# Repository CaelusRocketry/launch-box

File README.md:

View this project on [CADLAB.io](https://cadlab.io/project/25442). 

# Launch Box
Source code for our rocket's launch box.

# Pre-refactor
https://github.com/ProjectCaelus/launch-box/tree/2eb651392b1af030fa2c863ca12c2973148bd2ff

# Making Changes
Post-production version of PCBs: those currently in use are in launch-box\_stable folders. You shouldn't be editing these files, only copying them or using them as reference
Libraries now stores all our libraries
2 schematic libraries: CaelusPCB.lib and Launchbox.lib
1 Footprint library: Launchbox.pretty
If you intend to make a change to a PCB, copy the most recent version's project directory, in this case it should be those in _stable, rename, and move it to launch-box\PCBs\{corresponding folder}
Follow the naming conventions: Date + Time + Name
First off, it's important that you know what files you should and should not edit.
There are 3 kinds of libraries:

1.) -.lib: Looks like CaelusPCB.lib or Launchbox.lib
These are our stable global project libraries, meaning that they are like the framework for all components in all projects

2.) -cache.lib
When you copy a project directory, its -cache.lib file is copied with it. If you make changes to the schematic, for example adding a new component, the local -cache.lib file will update. The -cache.lib of the copied project remains the same, and this is how we do version control.
You don't need to really know how this process works or why its important. You just need to know that you add components to -.lib directories. YOU DON'T TOUCH -cache.lib or -rescue.lib.

3.) -rescue.lib
Not important until you're ready to publish/push your changes.
Whenever you copy a new project, or pull from github, YOU NEED TO CHECK YOUR LIBRARIES
Make sure that you have CaelusPCB.lib or Launchbox.lib (depending on what project you're working on, pointing to launch-box\Libraries\CaelusPCB.lib or Launchbox.lib
Make sure in Manage Footprints libraries, you have launch-box\Libaries\launchbox.pretty
Make sure the -cache and -rescue files are in the correct project directory: not from the copied one or something random
When you're finished on a project, you need to do the following:

1.) Make sure everything is saved, close and reopen KiCad

2.) Delete, not uncheck, Delete Launchbox.lib and/or CaelusPCB.lib from your library preferences and reopen the schematic.

3.) You should be prompted to rescue your -cached files. Say ok to all.

  This updates your -rescue.lib and sets all your schematic components to read from -rescue.lib instead of CaelusPCB.lib or Launchbox.lib
  This means this project is now isolated: a change in the global project libraries won't change your project

4.) Message avionics lead to verify and git push.

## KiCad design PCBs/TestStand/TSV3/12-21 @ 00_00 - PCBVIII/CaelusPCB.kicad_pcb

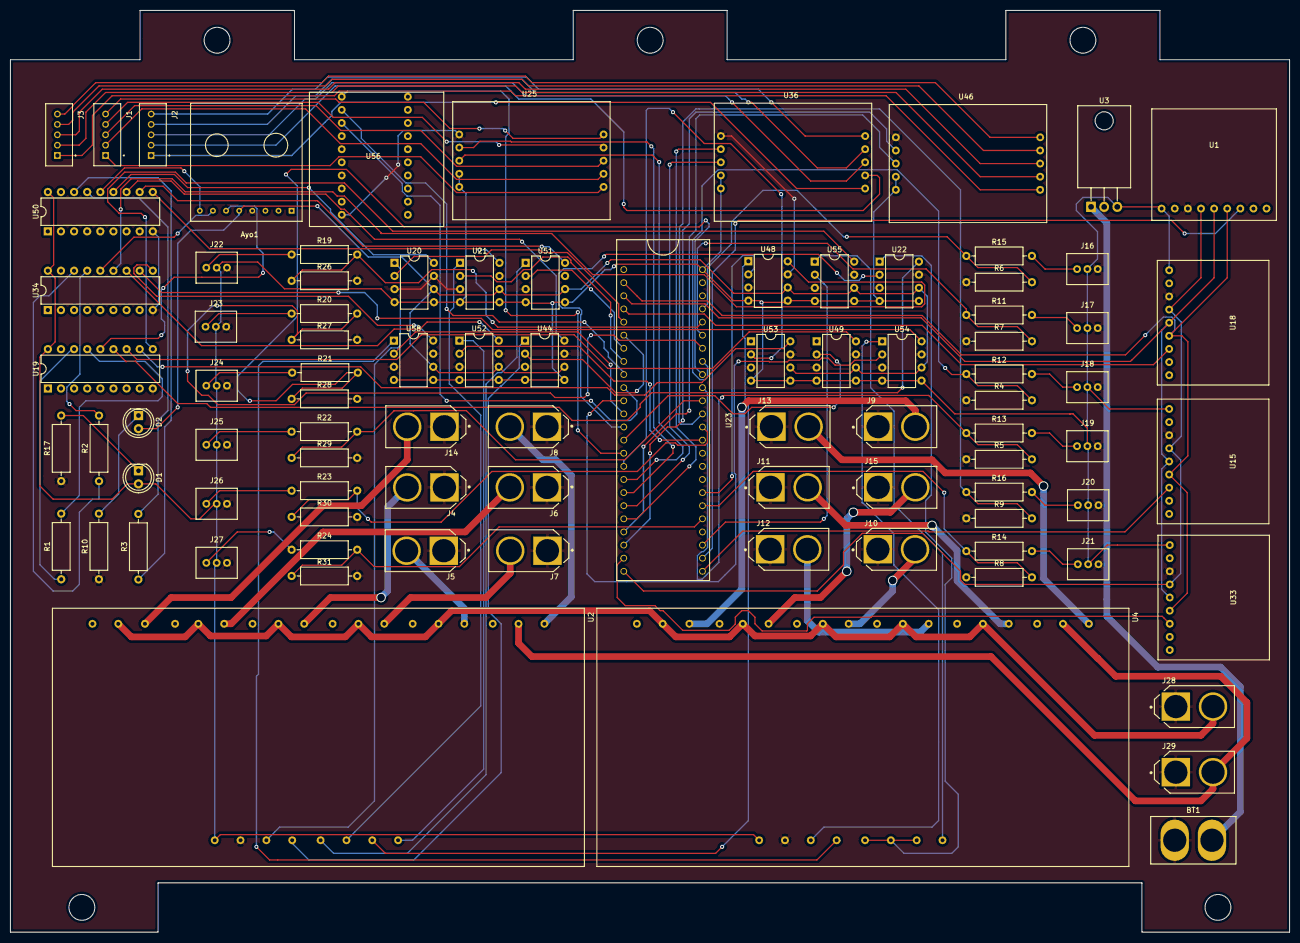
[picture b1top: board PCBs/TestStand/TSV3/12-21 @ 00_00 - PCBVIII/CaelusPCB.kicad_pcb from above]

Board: 2 copper layers, 247.7 x 178.4 mm, 89 parts (0 on the bottom side), 118 nets.

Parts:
Ayo1: RJ45EthernetBreakout
BT1: Battery_Cell; XT60H-M12
D1, D2: LED; LED_D5.0mm
J1, J2, J3: 440055-5; TE_1735446-5
J4, J5, J6, J7, J8, J9, J10, J11, J12, J13, J14, J15: XT60-M; AMASS_XT60-M
J16, J17, J18, J19, J20, J21, J22, J23, J24, J25, J26, J27: 440055-3; Crimp_Header
J28, J29: CaelusPCB-rescue_XT60-M-CaelusPCB; AMASS_XT60-M
R1, R2, R3, R4, R5, R6, R7, R8, R9, R11, R12, R13, R14, R15, R16, R19, R20, R21, R22, R23, R24, R26, R27, R28, R29, R30, R31: R_US; R_Axial_DIN0309_L9.0mm_D3.2mm_P12.70mm_Horizontal
R10, R17: R; R_Axial_DIN0309_L9.0mm_D3.2mm_P12.70mm_Horizontal
U1, U15, U18, U33: MAX31856
U2, U4: 6-Channel-5V-Relays; 6x_relay_module
U3: L7805; TO-220-3_Horizontal_TabDown
U19, U34, U50: Launchbox_HT12D; DIP-18_W7.62mm
U20, U21, U22, U44, U48, U49, U51, U52, U53, U54, U55, U58: SPDT_IC; DIP-8_W7.62mm
U23: Teensy3.6; Teensy 3.6
U25, U36, U46: LoadCellAmp
U56: XBee_Breakout; Xbee_Breakout

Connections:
1: U1.4, U15.4, U18.4, U23.32, U33.4
2: U23.31, U33.7
3: U20.2, U23.3
3.3: U23.47, U56.1
4: U23.4, U44.2
5: U23.5, U51.2
6: U21.2, U23.6
7: U23.39, U48.2
8: U23.13, U52.2
9: U23.9, U54.2
10: U23.10, U58.2
11: U22.2, U23.11
12: U23.12, U49.2
13: U1.6, U15.6, U18.6, U23.0, U33.6
14: U1.5, U15.5, U18.5, U23.1, U33.5
15: U18.7, U23.2
16: U23.25, U25.8
17: U23.26, U25.7
18: U23.27, U36.8
19: U23.28, U36.7
20: U23.29, U46.8
21: U23.30, U46.7
25: Ayo1.8, U50.14
26: Ayo1.7, U34.14
27: Ayo1.6, U19.14
28: U20.8, U50.13
29: U44.8, U50.12
30: U50.11, U51.8
31: U21.8, U50.10
32: U34.13, U48.8
33: U34.12, U52.8
34: U34.11, U54.8
35: U34.10, U58.8
36: U19.13, U22.8
37: U19.12, U49.8
38: U19.11, U53.8
39: U19.10, U55.8
40: U2.3, U20.1
41: U2.4, U44.1
42: U2.5, U51.1
43: U2.6, U21.1
44: U2.7, U48.1
45: U2.8, U52.1
46: U4.3, U54.1
47: U4.4, U58.1
48: U4.5, U4.6, U4.7, U22.1
50: U15.7, U23.33
51: U1.7, U23.34
52: Ayo1.5, D2.2, U20.6, U21.6, U22.6, U44.6, U48.6, U49.6, U51.6, U52.6, U53.6, U54.6, U55.6, U58.6
54: U4.8, U55.1
57: U23.24, U53.2
58: U23.35, U55.2
60: U23.8, U56.3
61: U23.7, U56.2
62: J4.2, U2.17
63: J7.2, U2.20
64: J5.2, U2.23
65: J8.2, U2.26
66: J9.2, U4.11
67: J15.2, U4.14
68: J10.2, U4.17
69: J12.2, U4.20
70: J11.2, U4.23
71: J13.2, U4.26
80: J14.2, U2.11
81: J6.2, U2.14
+5V: D1.2, J16.2, J17.2, J18.2, J19.2, J20.2, J21.2, J22.2, J23.2, J24.2, J25.2, J26.2, J27.2, U1.1, U2.1, U3.3, U4.1, U15.1, U18.1, U19.18, U20.4, U20.5, U21.4, U21.5, U22.4, U22.5, U23.40, U25.9, U25.10, U33.1, U34.18, U36.9, U36.10, U44.4, U44.5, U46.9, U46.10, U48.4, U48.5, U49.4, U49.5, U50.18, U51.4, U51.5, U52.4, U52.5, U53.4, U53.5, U54.4, U54.5, U55.4, U55.5, U58.4, U58.5
+12V: J28.2, U2.10, U2.13, U2.16, U2.19, U2.22, U4.10, U4.13, U4.16, U4.19, U4.22
+24V: J29.2, U2.25, U4.25
GND1: Ayo1.4, BT1.2, J4.1, J5.1, J6.1, J7.1, J8.1, J9.1, J10.1, J11.1, J12.1, J13.1, J14.1, J15.1, J16.3, J17.3, J18.3, J19.3, J20.3, J21.3, J22.3, J23.3, J24.3, J25.3, J26.3, J27.3, J28.1, J29.1, R4.1, R5.1, R6.1, R7.1, R8.1, R9.1, R10.1, R17.1, R26.2, R27.2, R28.2, R29.2, R30.2, R31.2, U1.3, U2.2, U3.2, U4.2, U15.3, U18.3, U19.9, U20.3, U20.7, U21.3, U21.7, U22.3, U22.7, U23.46, U25.6, U33.3, U34.9, U36.6, U44.3, U44.7, U46.6, U48.3, U48.7, U49.3, U49.7, U50.9, U51.3, U51.7, U52.3, U52.7, U53.3, U53.7, U54.3, U54.7, U55.3, U55.7, U56.10, U58.3, U58.7
unnamed: BT1.1, U3.1
unnamed: D1.1, R17.2
unnamed: D2.1, R10.2
unnamed: J1.1, U25.1
unnamed: J1.2, U25.2
unnamed: J1.3, U25.3
unnamed: J1.4, U25.4
unnamed: J1.5, U25.5
unnamed: J2.1, U36.1
unnamed: J2.2, U36.2
unnamed: J2.3, U36.3
unnamed: J2.4, U36.4
unnamed: J2.5, U36.5
unnamed: J3.1, U46.1
unnamed: J3.2, U46.2
unnamed: J3.3, U46.3
unnamed: J3.4, U46.4
unnamed: J3.5, U46.5
unnamed: J16.1, R15.2
unnamed: J17.1, R11.2
unnamed: J18.1, R12.2
unnamed: J19.1, R13.2
unnamed: J20.1, R16.2
unnamed: J21.1, R14.2
unnamed: J22.1, R19.1
unnamed: J23.1, R20.1
unnamed: J24.1, R21.1
unnamed: J25.1, R22.1
unnamed: J26.1, R23.1
unnamed: J27.1, R24.1
unnamed: R1.1, U19.16
unnamed: R1.2, U19.15
unnamed: R2.1, U34.16
unnamed: R2.2, U34.15
unnamed: R3.1, U50.16
unnamed: R3.2, U50.15
unnamed: R7.2, R11.1, U23.21
unnamed: R4.2, R12.1, U23.19
unnamed: R5.2, R13.1, U23.17
unnamed: R8.2, R14.1, U23.38
unnamed: R6.2, R15.1, U23.23
unnamed: R9.2, R16.1, U23.15
unnamed: R19.2, R26.1, U23.22
unnamed: R20.2, R27.1, U23.20
unnamed: R21.2, R28.1, U23.18
unnamed: R22.2, R29.1, U23.16
unnamed: R23.2, R30.1, U23.14
unnamed: R24.2, R31.1, U23.37

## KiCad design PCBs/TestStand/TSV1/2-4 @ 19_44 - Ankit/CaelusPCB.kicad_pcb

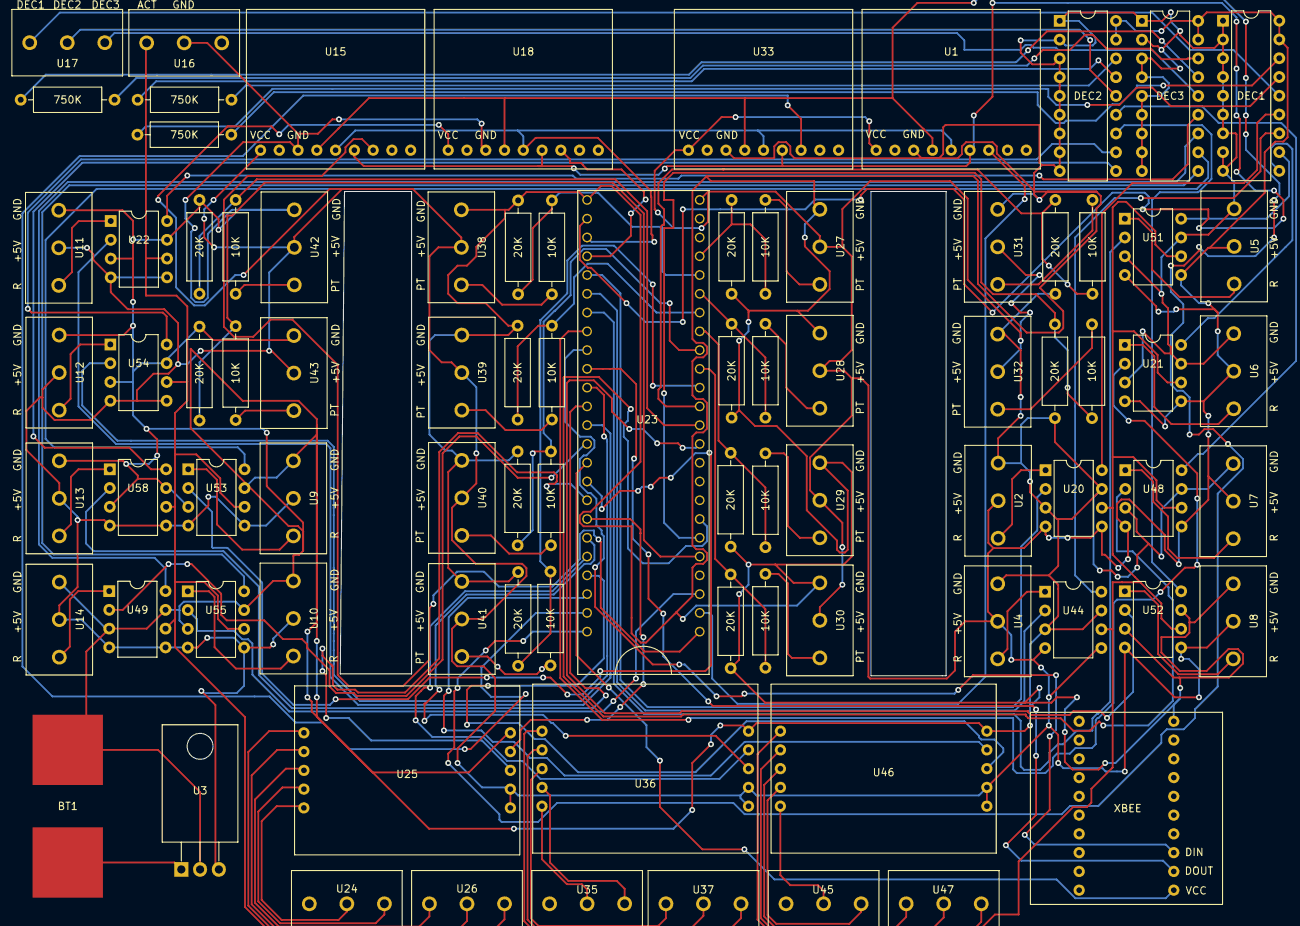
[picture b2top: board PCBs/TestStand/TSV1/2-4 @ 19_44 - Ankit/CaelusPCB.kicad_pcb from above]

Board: 2 copper layers, 85 parts (0 on the bottom side), 104 nets.

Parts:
10K, 10K#2, 10K#3, 10K#4, 10K#5, 10K#6, 10K#7, 10K#8, 10K#9, 10K#10, 10K#11, 10K#12, 20K, 20K#2, 20K#3, 20K#4, 20K#5, 20K#6, 20K#7, 20K#8, 20K#9, 20K#10, 20K#11, 20K#12, 750K, 750K#2, 750K#3: R_US; R_Axial_DIN0309_L9.0mm_D3.2mm_P12.70mm_Horizontal
BT1: Battery_Cell; Lipo_Battery_Connector
DEC1, DEC2, DEC3: Launchbox_HT12D; DIP-18_W7.62mm
U1, U15, U18, U33: MAX31856
U2, U4, U5, U6, U7, U8, U9, U10, U11, U12, U13, U14, U16, U17, U24, U26, U27, U28, U29, U30, U31, U32, U35, U37, U38, U39, U40, U41, U42, U43, U45, U47: SerialScrewTerminals; ScrewTerminals
U3: L7805; TO-220-3_Horizontal_TabDown
U20, U21, U22, U44, U48, U49, U51, U52, U53, U54, U55, U58: SPDT_IC; DIP-8_W7.62mm
U23: Teensy3.6; Teensy 3.6
U25, U36, U46: LoadCellAmp
XBEE: XBee_Breakout

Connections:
1: U1.4, U15.4, U18.4, U23.32, U33.4
2: U23.31, U33.7
3: U20.2, U23.3
3.3: U23.47, XBEE.1
4: U23.4, U44.2
5: U23.5, U51.2
6: U21.2, U23.6
7: U23.39, U48.2
8: U23.13, U52.2
9: U23.9, U54.2
10: U23.10, U58.2
11: U22.2, U23.11
12: U23.12, U49.2
13: U1.6, U15.6, U18.6, U23.0, U33.6
14: U1.5, U15.5, U18.5, U23.1, U33.5
15: U18.7, U23.2
16: U23.25, U25.8
17: U23.26, U25.7
18: U23.27, U36.8
19: U23.28, U36.7
20: U23.29, U46.8
21: U23.30, U46.7
25: DEC1.14, U17.1
26: DEC2.14, U17.2
27: DEC3.14, U17.3
28: DEC1.13, U20.8
29: DEC1.12, U44.8
30: DEC1.11, U51.8
31: DEC1.10, U21.8
32: DEC2.13, U48.8
33: DEC2.12, U52.8
34: DEC2.11, U54.8
35: DEC2.10, U58.8
36: DEC3.13, U22.8
37: DEC3.12, U49.8
38: DEC3.11, U53.8
39: DEC3.10, U55.8
40: U2.1, U20.1
41: U4.1, U44.1
42: U5.1, U51.1
43: U6.1, U21.1
44: U7.1, U48.1
45: U8.1, U52.1
46: U12.1, U54.1
47: U13.1, U58.1
48: U11.1, U22.1
49: U14.1, U49.1
50: U15.7, U23.33
51: U1.7, U23.34
52: U16.1, U20.6, U21.6, U22.6, U44.6, U48.6, U49.6, U51.6, U52.6, U53.6, U54.6, U55.6, U58.6
53: U9.1, U53.1
54: U10.1, U55.1
57: U23.24, U53.2
58: U23.35, U55.2
60: U23.7, XBEE.3
61: U23.8, XBEE.2
+5V: DEC1.17, DEC1.18, DEC2.17, DEC2.18, DEC3.17, DEC3.18, U1.1, U2.2, U3.3, U4.2, U5.2, U6.2, U7.2, U8.2, U9.2, U10.2, U11.2, U12.2, U13.2, U14.2, U15.1, U18.1, U20.4, U20.5, U21.4, U21.5, U22.4, U22.5, U23.40, U25.9, U25.10, U27.2, U28.2, U29.2, U30.2, U31.2, U32.2, U33.1, U36.9, U36.10, U38.2, U39.2, U40.2, U41.2, U42.2, U43.2, U44.4, U44.5, U46.9, U46.10, U48.4, U48.5, U49.4, U49.5, U51.4, U51.5, U52.4, U52.5, U53.4, U53.5, U54.4, U54.5, U55.4, U55.5, U58.4, U58.5
GND1: 20K.1, 20K#2.2, 20K#3.2, 20K#4.2, 20K#5.2, 20K#6.2, 20K#7.2, 20K#8.1, 20K#9.1, 20K#10.1, 20K#11.1, 20K#12.1, BT1.2, DEC1.1, DEC1.2, DEC1.3, DEC1.4, DEC1.5, DEC1.6, DEC1.7, DEC1.8, DEC1.9, DEC2.1, DEC2.2, DEC2.3, DEC2.4, DEC2.5, DEC2.6, DEC2.7, DEC2.8, DEC2.9, DEC3.1, DEC3.2, DEC3.3, DEC3.4, DEC3.5, DEC3.6, DEC3.7, DEC3.8, DEC3.9, U1.3, U2.3, U3.2, U4.3, U5.3, U6.3, U7.3, U8.3, U9.3, U10.3, U11.3, U12.3, U13.3, U14.3, U15.3, U16.2, U18.3, U20.3, U20.7, U21.3, U21.7, U22.3, U22.7, U23.46, U25.6, U27.3, U28.3, U29.3, U30.3, U31.3, U32.3, U33.3, U36.6, U38.3, U39.3, U40.3, U41.3, U42.3, U43.3, U44.3, U44.7, U46.6, U48.3, U48.7, U49.3, U49.7, U51.3, U51.7, U52.3, U52.7, U53.3, U53.7, U54.3, U54.7, U55.3, U55.7, U58.3, U58.7, XBEE.10
unnamed: BT1.1, U3.1
unnamed: 750K.1, DEC3.16
unnamed: 750K.2, DEC3.15
unnamed: 750K#2.1, DEC2.16
unnamed: 750K#2.2, DEC2.15
unnamed: 750K#3.1, DEC1.16
unnamed: 750K#3.2, DEC1.15
unnamed: 10K#12.1, 20K#9.2, U23.21
unnamed: 10K#12.2, U28.1
unnamed: 10K#11.1, 20K#12.2, U23.19
unnamed: 10K#11.2, U29.1
unnamed: 10K.1, 20K#11.2, U23.17
unnamed: 10K.2, U30.1
unnamed: 10K#10.1, 20K.2, U23.38
unnamed: 10K#10.2, U32.1
unnamed: 10K#9.1, 20K#10.2, U23.23
unnamed: 10K#9.2, U27.1
unnamed: 10K#8.1, 20K#8.2, U23.15
unnamed: 10K#8.2, U31.1
unnamed: 10K#7.1, U38.1
unnamed: 10K#7.2, 20K#7.1, U23.22
unnamed: 10K#6.1, U39.1
unnamed: 10K#6.2, 20K#6.1, U23.20
unnamed: 10K#5.1, U40.1
unnamed: 10K#5.2, 20K#5.1, U23.18
unnamed: 10K#4.1, U41.1
unnamed: 10K#4.2, 20K#4.1, U23.16
unnamed: 10K#3.1, U42.1
unnamed: 10K#3.2, 20K#3.1, U23.14
unnamed: 10K#2.1, U43.1
unnamed: 10K#2.2, 20K#2.1, U23.37
unnamed: U24.1, U25.4
unnamed: U24.2, U25.5
unnamed: U25.1, U26.1
unnamed: U25.2, U26.2
unnamed: U25.3, U26.3
unnamed: U35.1, U36.4
unnamed: U35.2, U36.5
unnamed: U36.1, U37.1
unnamed: U36.2, U37.2
unnamed: U36.3, U37.3
unnamed: U45.1, U46.4
unnamed: U45.2, U46.5
unnamed: U46.1, U47.1
unnamed: U46.2, U47.2
unnamed: U46.3, U47.3

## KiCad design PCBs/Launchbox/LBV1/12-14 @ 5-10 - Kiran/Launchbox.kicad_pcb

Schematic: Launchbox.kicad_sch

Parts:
BT1: Battery_Cell; Lipo_Battery_Connector
D1: LED; LED_D5.0mm
R1, R2, R3, R4, R5: R_US; R_Axial_DIN0207_L6.3mm_D2.5mm_P7.62mm_Horizontal
SW1, SW2, SW3, SW4, SW5, SW6, SW7, SW8, SW9, SW10, SW11, SW12: SW_SPDT_MSM; SPDT_Slide_Switch
SW13, SW14, SW15, SW16, SW17, SW18: SW_Push; Pushbutton
SW19, SW20: SW_Push
U1: Teensy3.6; Teensy 3.6
U2: L7805; TO-220F-3_Horizontal_TabDown
U3, U5, U6: HT12E
U7, U8: SerialScrewTerminals; ScrewTerminals

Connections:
3.3V: SW13.1, SW14.1, SW15.1, SW16.1, SW17.1, SW19.1, SW20.1, U1.42, U3.18, U5.18, U6.18
GND: BT1.2, R4.1, R5.1, SW1.2, SW2.2, SW3.2, SW4.2, SW5.2, SW6.2, SW7.2, SW8.2, SW9.2, SW10.2, SW11.2, SW12.2, U1.43, U1.46, U2.2, U3.9, U3.14, U5.9, U5.14, U6.9, U6.13, U6.14, U8.1
unnamed: D1.1 (K), R5.2
unnamed: D1.2 (A), R4.2, SW18.2, U8.2
unnamed: R1.1, U3.16
unnamed: R1.2, U3.15
unnamed: R2.1, U5.16
unnamed: R2.2, U5.15
unnamed: R3.1, U6.16
unnamed: R3.2, U6.15
unnamed: SW1.1, U1.0
unnamed: SW1.3, U1.1
unnamed: SW2.1, U1.2
unnamed: SW2.3, U1.3
unnamed: SW3.1, U1.4
unnamed: SW3.3, U1.5
unnamed: SW4.1, U1.6
unnamed: SW4.3, U1.7
unnamed: SW5.1, U1.8
unnamed: SW5.3, U1.9
unnamed: SW6.1, U1.10
unnamed: SW6.3, U1.11
unnamed: SW7.1, U1.12
unnamed: SW7.3, U1.24
unnamed: SW8.1, U1.25
unnamed: SW8.3, U1.26
unnamed: SW9.1, U1.27
unnamed: SW9.3, U1.28
unnamed: SW10.1, U1.29
unnamed: SW10.3, U1.30
unnamed: SW11.1, U1.31
unnamed: SW11.3, U1.32
unnamed: SW12.1, U1.35
unnamed: SW12.3, U1.36
unnamed: SW13.2, U1.37
unnamed: SW14.2, U1.38
unnamed: SW15.2, U1.39
unnamed: SW16.2, U1.45
unnamed: SW17.2, U1.44
unnamed: SW18.1, U1.40, U2.3
unnamed: SW19.2, U1.33
unnamed: SW20.2, U1.34
unnamed: U1.13, U6.12
unnamed: U1.14, U6.11
unnamed: U1.15, U6.10
unnamed: U1.16, U5.13
unnamed: U1.17, U5.12
unnamed: U1.18, U5.11
unnamed: U1.19, U5.10
unnamed: U1.20, U3.13
unnamed: U1.21, U3.12
unnamed: U1.22, U3.11
unnamed: U1.23, U3.10
unnamed: U3.17, U7.3
unnamed: U5.17, U7.2
unnamed: U6.17, U7.1
VCC: BT1.1, U2.1

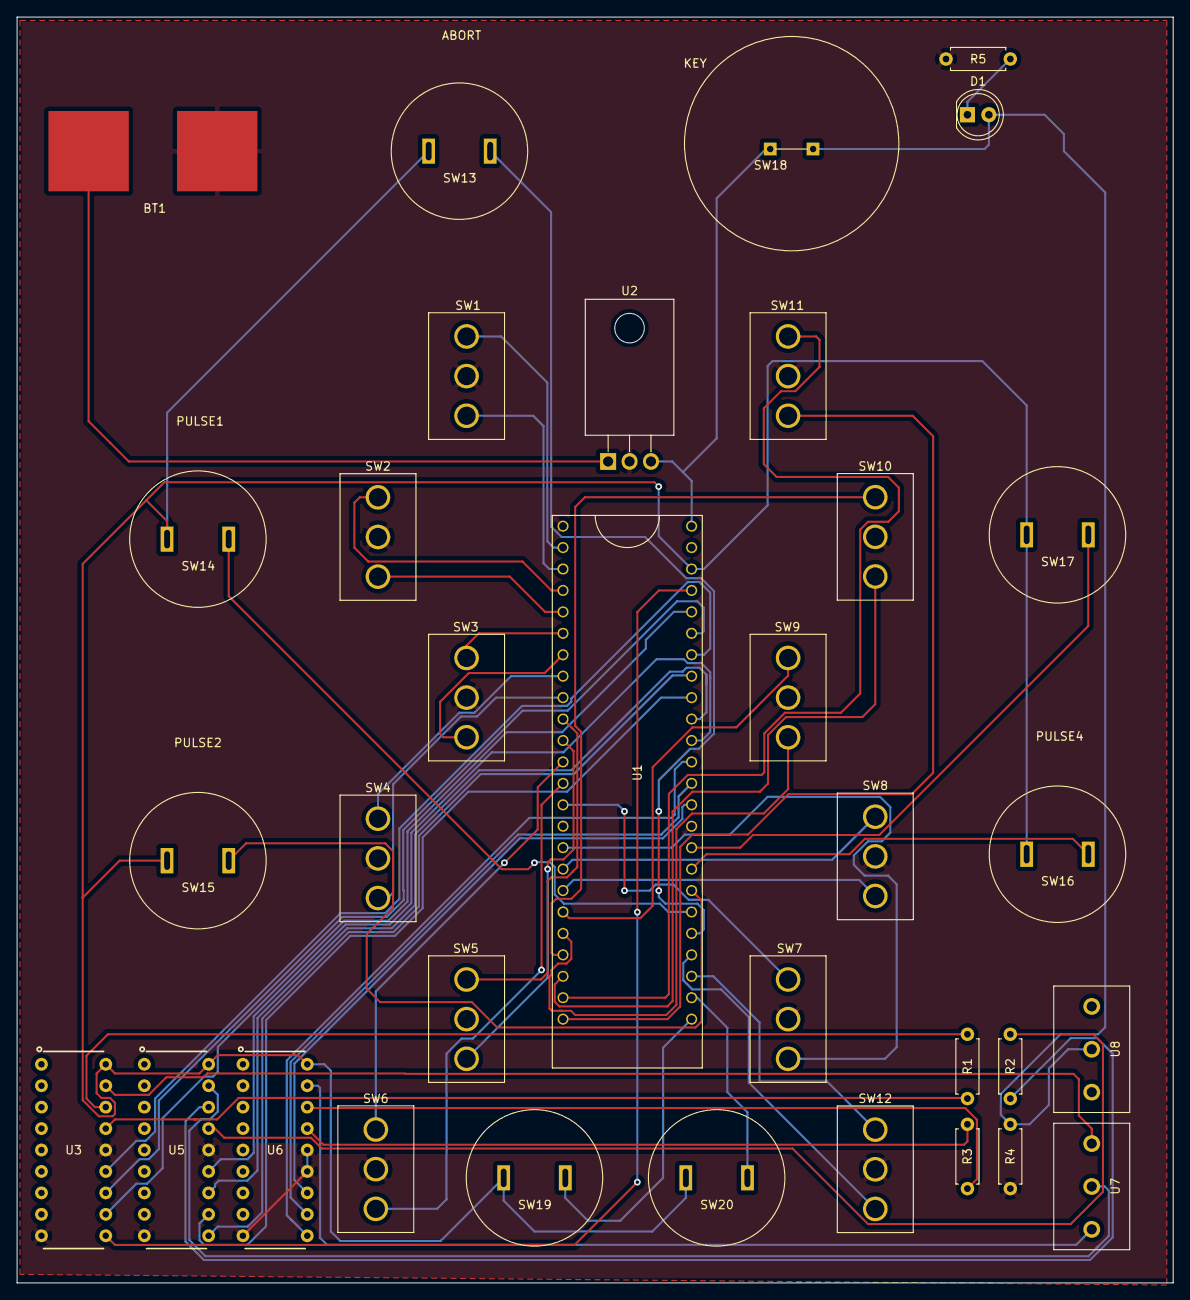
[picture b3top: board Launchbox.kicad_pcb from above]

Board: 2 copper layers, 137.0 x 150.0 mm, 34 parts (0 on the bottom side), 57 nets.

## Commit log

2020-10-01 Add launchbox files
2020-11-14 Follow Arduino file format
2020-11-22 added pcb stuff
2020-11-24 Add files via upload
    GND1 pins connected
2020-11-25 Connected, organized
2020-11-27 test stand pcb done!
2020-11-30 v1 PCBs fully done, ordered 11/29. gerbers in respective project folders
2021-01-16 Change pin values
2021-01-18 test stand pcb v2 uploaded
2021-01-20 added ground, vcc, and some load cell traces
2021-01-20 finished adding traces for all components.
2021-01-22 Add tested launch box code
2021-01-23 Add modified launchbox printing and testing receiver Arduino code
2021-01-23 Srikar writes good code
2021-03-18 Updates Pin Names
2021-03-18 Changed send_message protocol
2021-03-18 Moved Valve Arduino Code To Launchbox
2021-03-18 Fix some syntax errors
2021-03-18 Add some docs
2021-03-18 Clarify main loop code
2021-03-18 Fix loop
2021-03-18 Remove old serial variables
2021-03-18 Clean up code
2021-03-18 Add notes to readLaunchboxSwitch
2021-03-20 Remove ValveArduino code and rewrite launchbox code to handle pulsing and special
2021-03-20 Add comments to launch box code
2021-03-20 Fix small comment issue
2021-03-29 added all pcbs
2021-04-05 Add working TESTED launch box code with relays; need to update config.h for special/pulse
2021-04-08 Alternate actuation type based on switch pins
2021-04-11 Add updated constants.h (reversed switch direction and fixed bugs)
2021-04-17 Using unfried pins
2021-04-19 Add back original documented LB teensypins
2021-05-08 Add basic autosequence functionality
2021-05-08 Update constants
2021-05-08 Fix code
2021-05-08 Fix launchbox again
2021-05-09 Add full autosequence functionality code
2021-05-30 Working LB code
2021-06-07 launch-box code updated with igniter push button
2021-06-07 random changes
2021-06-11 Launchbox push buttons wired to 3.3V instead of 5V.
2021-06-13 Fixed compile errors and constants.h
2021-06-14 footprint error fixed
2021-06-14 Footprint error fixed.
2021-06-18 Header connectors wired in schematic
2021-06-28 layout 6/28
2021-06-29 Tracing 6/29
2021-06-30 Add traces
2021-06-30 6/30 @ 0:51 - Eric
2021-06-30 renamed
2021-06-30 file reallocation
2021-06-30 minor fixes
2021-06-30 some traces
2021-07-01 Revamp finished 7/1 @ 10:15
2021-07-09 Final PCBII 7-9 @1609 - Eric Feng
2021-07-10 Created GND plane and generated grbrs
2021-07-26 launchbox final changes 7-25 @22:09
2021-07-31 final LB and TS
2021-08-02 update teensy footprint TS
2021-08-05 reorganized
2021-08-22 PDB revamp
2021-08-22 PDB Final 8/22/21 @18:06
2021-08-24 Enlarged solder pad and hole sizes
2021-09-06 Don't Touch TS_Current
2021-09-11 Random updates
2021-09-12 updated launchbox config
2021-09-12 updated constants
2021-09-12 added functionality to 4 more switches
2021-09-13 LB Code:all switches accounted for
2021-10-03 updated launch-box code
2021-10-20 Major file structure change
2021-10-29 RJ45EthernetBreakout footprint added to Launchbox.pretty
2021-10-30 libraries
2021-11-06 adding rescued files to stable
2021-11-20 Adds Ethernet Breakout Board
2021-11-27 Adds Updated RJ45 Ethernet Breakout Board
2021-11-28 Adds RJ45 EBB to Schematic & PCB
2021-11-29 Hello, nice to meet you! This adds cache and rescue :)))
2021-11-29 fixed stable folder
2021-12-01 :DDD
2021-12-04 Replace battery pads with XT-60
2021-12-05 Update fp-info-cache
2021-12-08 Update trace for XT-60
2021-12-11 Wires Ethernet Breakout Board
2021-12-11 Cleanup
2021-12-11 Maintenance update
2021-12-12 Added 2 buttons to schematic and footprint (SW19/20)
2021-12-13 Ethernet Breakout Board Updates
2021-12-19 Ready To Go Update!
2021-12-19 Fixed keyswitch footprint
2021-12-19 Whoops
2021-12-19 Add PDB to schematic
2021-12-20 hellooo
2021-12-20 Schematic Wiring/Clean-Up
2021-12-20 DRC Fix
2021-12-20 Add new footprints :D
2021-12-20 Assign the last symbols to footprints
2021-12-20 Sowweee Anish
2021-12-20 Triple MPV
2021-12-20 :DDDD
2021-12-21 Add layout attempt #1 (we tried!!)
2021-12-21 minor changes to pcb layout
2021-12-21 Flippy a Couple Components
2021-12-21 Teensy Footprint Fix
2021-12-21 PTs maybe
2021-12-21 Updates crimp header
2021-12-21 Fix relay footprint
2021-12-21 PDB to Relays Wiring
2021-12-21 I changed one wire, I am a pro lmao imgaine not being as good as me ;)
2021-12-21 I added a wire
2021-12-21 Connected some relay wires
2021-12-21 Fixed a few of the DAMN impassable barriers
2021-12-21 PDB & Relays
2021-12-21 Add wishy washy washing machine stuff for #shift no. 2
2021-12-21 Analog Switches & Encoders
2021-12-21 Add Xbee and Load Cell Amps #shift no. 4!!
2021-12-21 YES ALMOST DONE WITH WIRING
2021-12-21 Fix DRC and kinda edgecuts
2021-12-21 Edge Cuts!
2021-12-21 fix valves to no port on relays
2021-12-21 Fix Design rule failures
2021-12-21 Some lines here and there!
2022-01-15 PCB Layout Parentheses Issue
2022-01-15 Fixed voltage regulator on TSPCBV4
2022-01-15 fix lb code
2022-01-15 updated lb code
2022-01-19 new launchbox directory
2022-01-20 lbv2 cache and rescue files
2022-01-20 Adds Ethernet Breakout Board to LB PCB
2022-01-20 Updates Voltage Regulator on LB PCB
2022-01-21 Changed battery pads to XT-60MH, and added XT-60MH part to Launchbox.lib
2022-01-21 Organization
2022-01-22 Whoops Accidentally Ignored
2022-01-22 Added new keyswitch to PCB with new pads
2022-01-22 key switch pin size set
2022-01-22 key switch hole size enlarged
2022-01-23 final launchbox
2022-01-23 Launchbox v2 Final Update!
2022-03-12 Cad :(
    Uploaded cad and linked LB footprints to cad so 3d model works.
2022-03-12 PCBV2 3D Model - files and footprint edits ._.
2022-03-12 3d on pcb v3 (acc v4) looks fire
2022-03-12 Forgot to save TSPCBv2... oops
2022-04-16 Backlink to CADLAB.io has been added.
2022-04-23 Initial refactor changes:
    - Removed old backups
    - Organized PCB versions by major version number
    - Removed unnecessary files (.DS_Store) and added them to .gitignore
    - Deleted duplicates of Libraries (Launchbox.pretty, kicad-footprints-master)
    - Re-organize 3D Models (STEP files)
2022-04-24 Removed (outdated) launch-box-self-recv per Adi's request
2022-05-19 Beginning Callisto Dev!
2022-05-21 Removes Callisto_Dev Folder and Reorganizes 3D_Models\Other
2022-07-09 Add lbv3 schematic
2022-07-14 Schematic Update
2022-07-22 changed special valve opening times to 5 seconds
2022-08-13 Replace teensy with rpi
2022-08-14 Replace existing switches
2022-09-17 ca
    Com
2022-10-15 commit
    k
2022-10-30 Add TS cache and rescue libraries
2022-10-30 Update libraries
2022-11-05 Added ethernet schematic
2022-11-05 Add ethernet edge cuts
2023-04-03 Fix schematic + finalize launchbox
